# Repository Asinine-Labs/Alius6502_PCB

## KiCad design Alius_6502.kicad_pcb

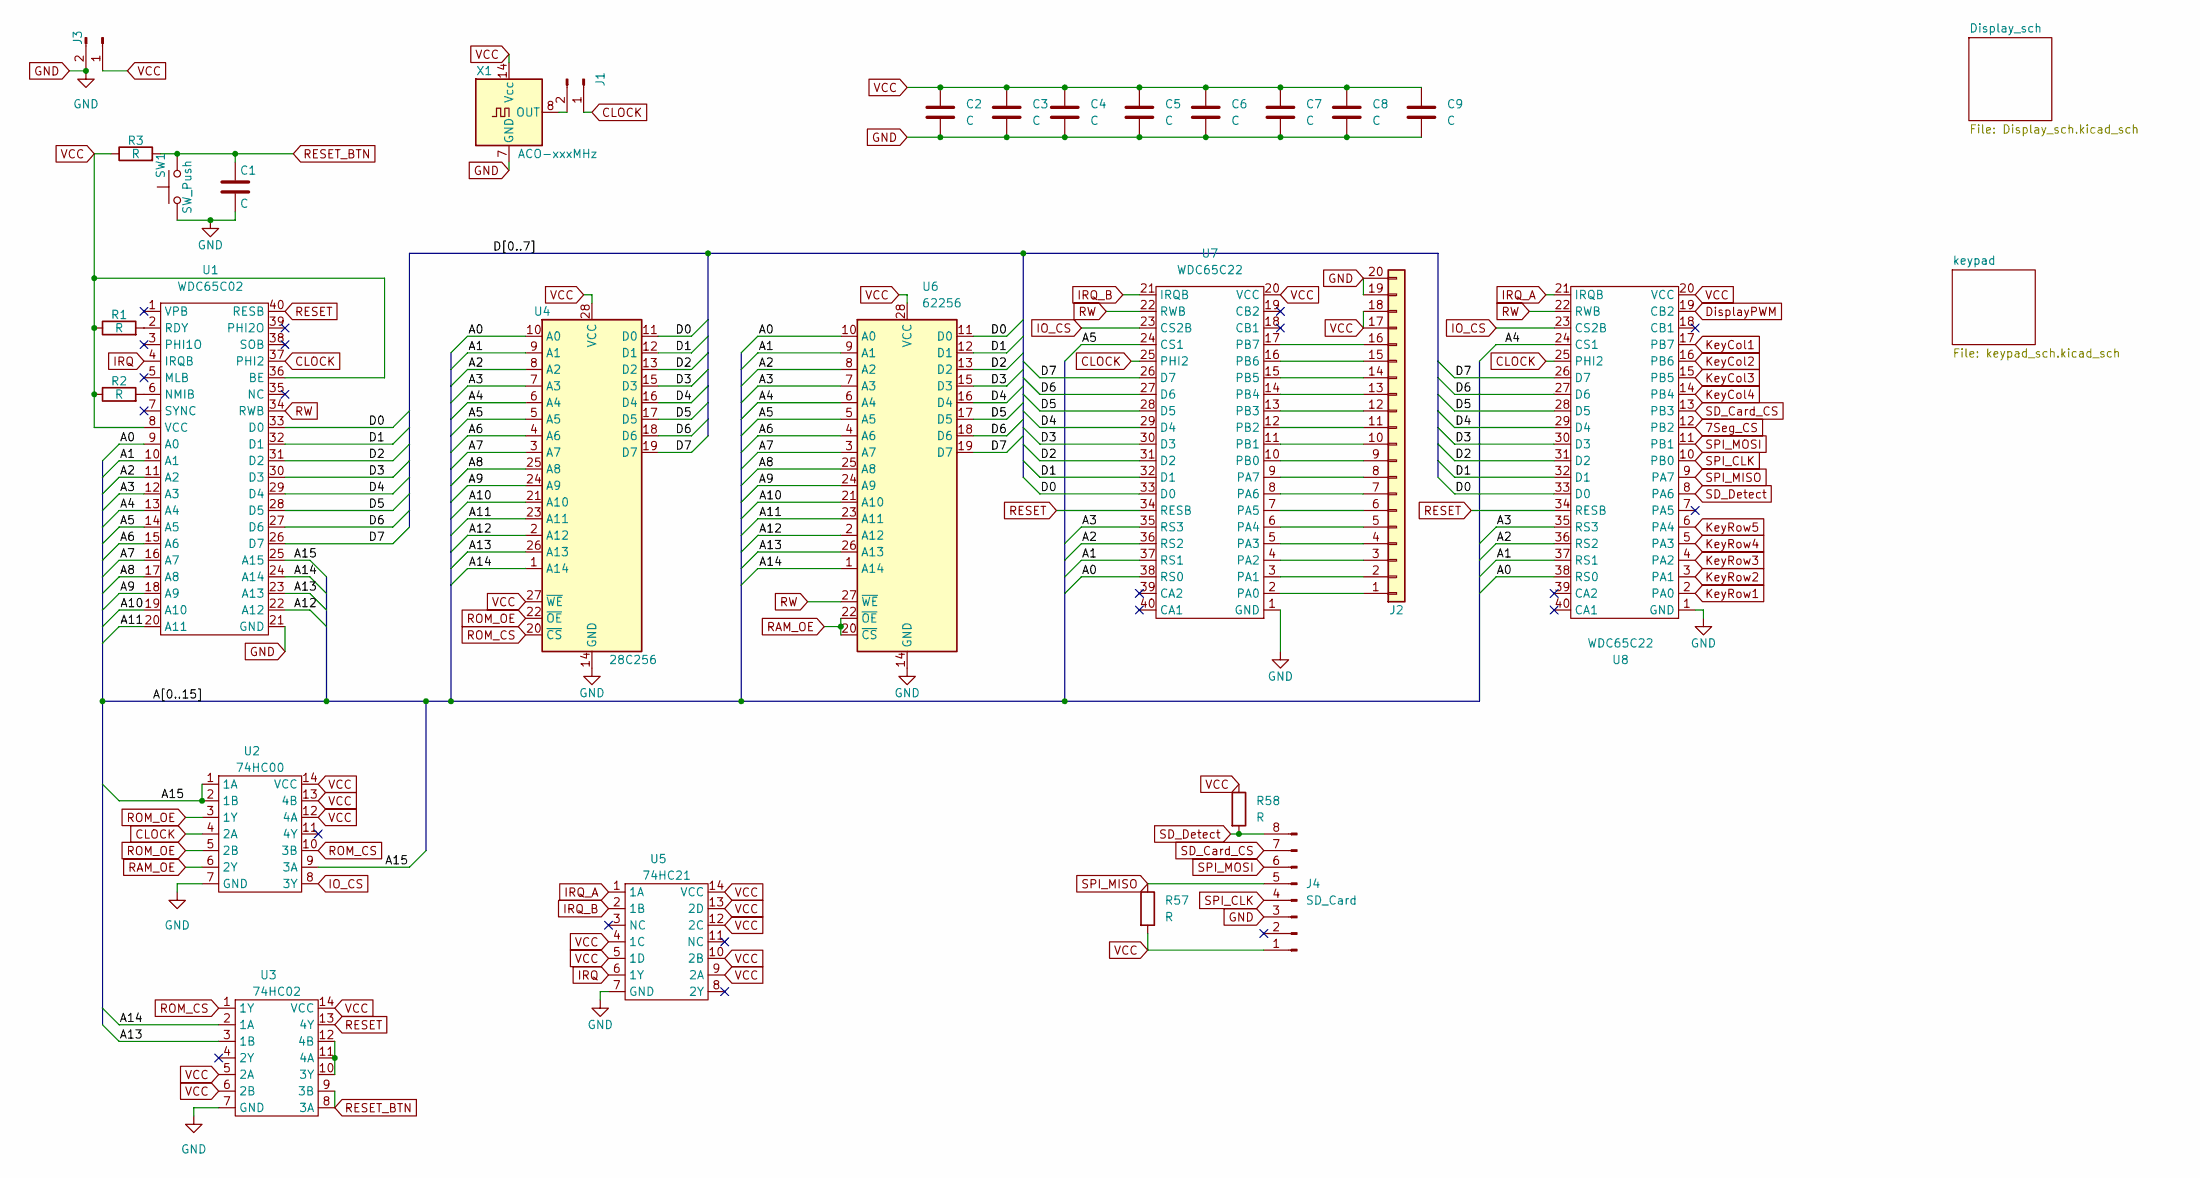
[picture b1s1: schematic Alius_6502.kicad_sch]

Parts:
C1: C; CP_Radial_D6.3mm_P2.50mm
C2, C3, C4, C5, C6, C7, C8, C9: C; C_Axial_L3.8mm_D2.6mm_P7.50mm_Horizontal
J1: Conn_01x02_Male; 2_pin_header
J2: Conn_01x20; 20pin header
J3: Power; 2_pin_header
J4: SD_Card; SD_Card_Header
R1, R2, R3, R57, R58: R; R_Axial_DIN0207_L6.3mm_D2.5mm_P10.16mm_Horizontal
SW1: SW_Push; push_switch
U1: WDC65C02; 40-pin-DIP
U2: 74HC00; DIP-14_W7.62mm_Socket_LongPads
U3: 74HC02; DIP-14_W7.62mm_Socket_LongPads
U4: 28C256; 28-pin-DIP
U5: 74HC21; DIP-14_W7.62mm_Socket_LongPads
U6: 62256; 28-pin-DIP
U7, U8: WDC65C22; 40-pin-DIP
X1: ACO-xxxMHz; Oscillator_DIP-14

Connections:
7Seg_CS: U8.12 (PB2); also elsewhere on the board
/A0: U1.9 (A0), U4.10 (A0), U6.10 (A0), U7.38 (RS0), U8.38 (RS0)
/A1: U1.10 (A1), U4.9 (A1), U6.9 (A1), U7.37 (RS1), U8.37 (RS1)
/A2: U1.11 (A2), U4.8 (A2), U6.8 (A2), U7.36 (RS2), U8.36 (RS2)
/A3: U1.12 (A3), U4.7 (A3), U6.7 (A3), U7.35 (RS3), U8.35 (RS3)
/A4: U1.13 (A4), U4.6 (A4), U6.6 (A4), U8.24 (CS1)
/A5: U1.14 (A5), U4.5 (A5), U6.5 (A5), U7.24 (CS1)
/A6: U1.15 (A6), U4.4 (A6), U6.4 (A6)
/A7: U1.16 (A7), U4.3 (A7), U6.3 (A7)
/A8: U1.17 (A8), U4.25 (A8), U6.25 (A8)
/A9: U1.18 (A9), U4.24 (A9), U6.24 (A9)
/A10: U1.19 (A10), U4.21 (A10), U6.21 (A10)
/A11: U1.20 (A11), U4.23 (A11), U6.23 (A11)
/A12: U1.22 (A12), U4.2 (A12), U6.2 (A12)
/A13: U1.23 (A13), U3.3 (1B), U4.26 (A13), U6.26 (A13)
/A14: U1.24 (A14), U3.2 (1A), U4.1 (A14), U6.1 (A14)
/A15: U1.25 (A15), U2.1 (1A), U2.2 (1B), U2.9 (3A)
/D0: U1.33 (D0), U4.11 (D0), U6.11 (D0), U7.33 (D0), U8.33 (D0)
/D1: U1.32 (D1), U4.12 (D1), U6.12 (D1), U7.32 (D1), U8.32 (D1)
/D2: U1.31 (D2), U4.13 (D2), U6.13 (D2), U7.31 (D2), U8.31 (D2)
/D3: U1.30 (D3), U4.15 (D3), U6.15 (D3), U7.30 (D3), U8.30 (D3)
/D4: U1.29 (D4), U4.16 (D4), U6.16 (D4), U7.29 (D4), U8.29 (D4)
/D5: U1.28 (D5), U4.17 (D5), U6.17 (D5), U7.28 (D5), U8.28 (D5)
/D6: U1.27 (D6), U4.18 (D6), U6.18 (D6), U7.27 (D6), U8.27 (D6)
/D7: U1.26 (D7), U4.19 (D7), U6.19 (D7), U7.26 (D7), U8.26 (D7)
CLOCK: J1.1, U1.37 (PHI2), U2.4 (2A), U7.25 (PHI2), U8.25 (PHI2)
DisplayPWM: U8.19 (CB2); also elsewhere on the board
GND: C1.2, C2.2, C3.2, C4.2, C5.2, C6.2, C7.2, C8.2, C9.2, J2.19, J2.20, J3.2, J4.3, SW1.1, U1.21 (GND), U2.7 (GND), U3.7 (GND), U4.14 (GND), U5.7 (GND), U6.14 (GND), U7.1 (GND), U8.1 (GND), X1.7 (GND); also elsewhere on the board
IO_CS: U2.8 (3Y), U7.23 (CS2B), U8.23 (CS2B)
IRQ: U1.4 (IRQB), U5.6 (1Y)
IRQ_A: U5.1 (1A), U8.21 (IRQB)
IRQ_B: U5.2 (1B), U7.21 (IRQB)
KeyCol1: U8.17 (PB7); also elsewhere on the board
KeyCol2: U8.16 (PB6); also elsewhere on the board
KeyCol3: U8.15 (PB5); also elsewhere on the board
KeyCol4: U8.14 (PB4); also elsewhere on the board
KeyRow1: U8.2 (PA0); also elsewhere on the board
KeyRow2: U8.3 (PA1); also elsewhere on the board
KeyRow3: U8.4 (PA2); also elsewhere on the board
KeyRow4: U8.5 (PA3); also elsewhere on the board
KeyRow5: U8.6 (PA4); also elsewhere on the board
unnamed: J1.2, X1.8 (OUT)
unnamed: J2.1, U7.2 (PA0)
unnamed: J2.2, U7.3 (PA1)
unnamed: J2.3, U7.4 (PA2)
unnamed: J2.4, U7.5 (PA3)
unnamed: J2.5, U7.6 (PA4)
unnamed: J2.6, U7.7 (PA5)
unnamed: J2.7, U7.8 (PA6)
unnamed: J2.8, U7.9 (PA7)
unnamed: J2.9, U7.10 (PB0)
unnamed: J2.10, U7.11 (PB1)
unnamed: J2.11, U7.12 (PB2)
unnamed: J2.12, U7.13 (PB3)
unnamed: J2.13, U7.14 (PB4)
unnamed: J2.14, U7.15 (PB5)
unnamed: J2.15, U7.16 (PB6)
unnamed: J2.16, U7.17 (PB7)
unnamed: R2.2, U1.6 (NMIB)
unnamed: R1.2, U1.2 (RDY)
unnamed: U3.10 (3Y), U3.11 (4A), U3.12 (4B)
RAM_OE: U2.6 (2Y), U6.20 (~CS), U6.22 (~OE)
RESET: U1.40 (RESB), U3.13 (4Y), U7.34 (RESB), U8.34 (RESB); also elsewhere on the board
RESET_BTN: C1.1, R3.2, SW1.2, U3.8 (3A), U3.9 (3B)
ROM_CS: U2.10 (3B), U3.1 (1Y), U4.20 (~CS)
ROM_OE: U2.3 (1Y), U2.5 (2B), U4.22 (~OE)
RW: U1.34 (RWB), U6.27 (~WE), U7.22 (RWB), U8.22 (RWB)
SD_Card_CS: J4.7, U8.13 (PB3)
SD_Detect: J4.8, R58.2, U8.8 (PA6)
SPI_CLK: J4.4, U8.10 (PB0); also elsewhere on the board
SPI_MISO: J4.5, R57.1, U8.9 (PA7)
SPI_MOSI: J4.6, U8.11 (PB1); also elsewhere on the board
VCC: C2.1, C3.1, C4.1, C5.1, C6.1, C7.1, C8.1, C9.1, J2.17, J2.18, J3.1, J4.1, R1.1, R2.1, R3.1, R57.2, R58.1, U1.8 (VCC), U1.36 (BE), U2.12 (4A), U2.13 (4B), U2.14 (VCC), U3.5 (2A), U3.6 (2B), U3.14 (VCC), U4.27 (~WE), U4.28 (VCC), U5.4 (1C), U5.5 (1D), U5.9 (2A), U5.10 (2B), U5.12 (2C), U5.13 (2D), U5.14 (VCC), U6.28 (VCC), U7.20 (VCC), U8.20 (VCC), X1.14 (Vcc); also elsewhere on the board

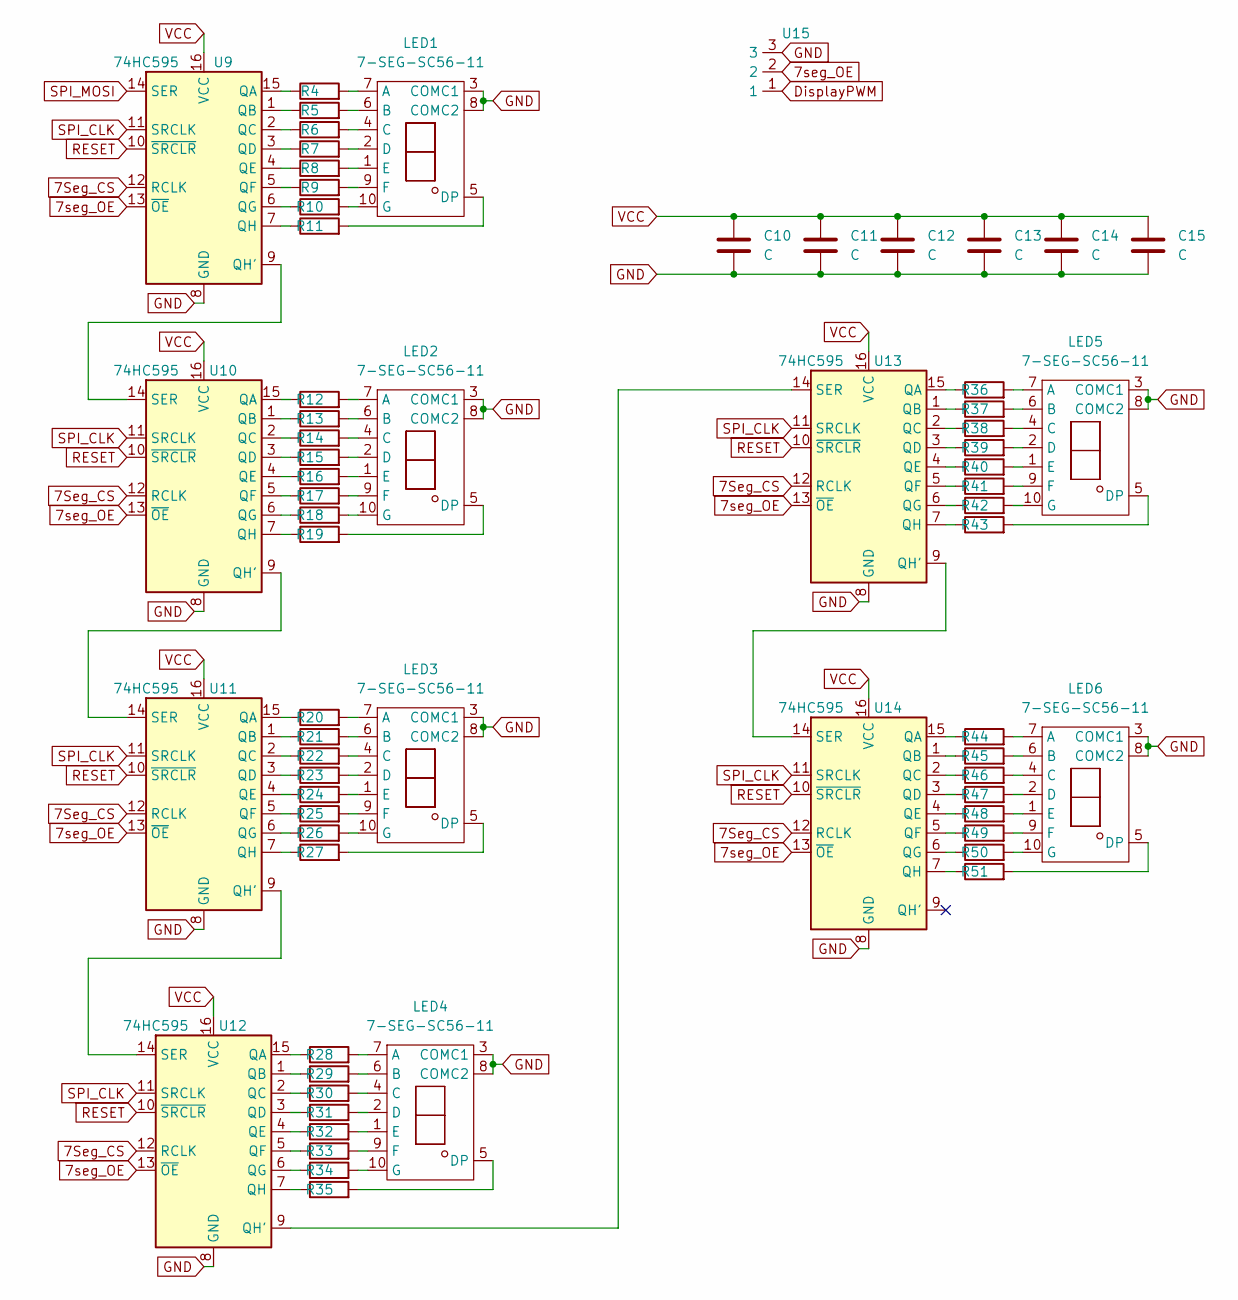
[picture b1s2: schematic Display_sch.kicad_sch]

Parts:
C10, C11, C12, C13, C14, C15: C; C_Axial_L3.8mm_D2.6mm_P7.50mm_Horizontal
LED1, LED2, LED3, LED4, LED5, LED6: 7-SEG-SC56-11; 7-seg
R4, R5, R6, R7, R8, R9, R10, R11, R12, R13, R14, R15, R16, R17, R18, R19, R20, R21, R22, R23, R24, R25, R26, R27, R28, R29, R30, R31, R32, R33, R34, R35, R36, R37, R38, R39, R40, R41, R42, R43, R44, R45, R46, R47, R48, R49, R50, R51: R; R_Axial_DIN0207_L6.3mm_D2.5mm_P10.16mm_Horizontal
U9, U10, U11, U12, U13, U14: 74HC595; DIP-16_W7.62mm_LongPads
U15: 3_pin_header

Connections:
7Seg_CS: U9.12 (RCLK), U10.12 (RCLK), U11.12 (RCLK), U12.12 (RCLK), U13.12 (RCLK), U14.12 (RCLK); also elsewhere on the board
7seg_OE: U9.13 (~OE), U10.13 (~OE), U11.13 (~OE), U12.13 (~OE), U13.13 (~OE), U14.13 (~OE), U15.2; also elsewhere on the board
GND: C10.2, C11.2, C12.2, C13.2, C14.2, C15.2, LED1.3 (COMC1), LED1.8 (COMC2), LED2.3 (COMC1), LED2.8 (COMC2), LED3.3 (COMC1), LED3.8 (COMC2), LED4.3 (COMC1), LED4.8 (COMC2), LED5.3 (COMC1), LED5.8 (COMC2), LED6.3 (COMC1), LED6.8 (COMC2), U9.8 (GND), U10.8 (GND), U11.8 (GND), U12.8 (GND), U13.8 (GND), U14.8 (GND), U15.3; also elsewhere on the board
unnamed: LED1.7 (A), R4.2
unnamed: LED1.6 (B), R5.2
unnamed: LED1.4 (C), R6.2
unnamed: LED1.2 (D), R7.2
unnamed: LED1.5 (DP), R11.2
unnamed: LED1.1 (E), R8.2
unnamed: LED1.9 (F), R9.2
unnamed: LED1.10 (G), R10.2
unnamed: LED2.7 (A), R12.2
unnamed: LED2.6 (B), R13.2
unnamed: LED2.4 (C), R14.2
unnamed: LED2.2 (D), R15.2
unnamed: LED2.5 (DP), R19.2
unnamed: LED2.1 (E), R16.2
unnamed: LED2.9 (F), R17.2
unnamed: LED2.10 (G), R18.2
unnamed: LED3.7 (A), R20.2
unnamed: LED3.6 (B), R21.2
unnamed: LED3.4 (C), R22.2
unnamed: LED3.2 (D), R23.2
unnamed: LED3.5 (DP), R27.2
unnamed: LED3.1 (E), R24.2
unnamed: LED3.9 (F), R25.2
unnamed: LED3.10 (G), R26.2
unnamed: LED4.7 (A), R28.2
unnamed: LED4.6 (B), R29.2
unnamed: LED4.4 (C), R30.2
unnamed: LED4.2 (D), R31.2
unnamed: LED4.5 (DP), R35.2
unnamed: LED4.1 (E), R32.2
unnamed: LED4.9 (F), R33.2
unnamed: LED4.10 (G), R34.2
unnamed: LED5.7 (A), R36.2
unnamed: LED5.6 (B), R37.2
unnamed: LED5.4 (C), R38.2
unnamed: LED5.2 (D), R39.2
unnamed: LED5.5 (DP), R43.2
unnamed: LED5.1 (E), R40.2
unnamed: LED5.9 (F), R41.2
unnamed: LED5.10 (G), R42.2
unnamed: LED6.7 (A), R44.2
unnamed: LED6.6 (B), R45.2
unnamed: LED6.4 (C), R46.2
unnamed: LED6.2 (D), R47.2
unnamed: LED6.5 (DP), R51.2
unnamed: LED6.1 (E), R48.2
unnamed: LED6.9 (F), R49.2
unnamed: LED6.10 (G), R50.2
unnamed: R4.1, U9.15 (QA)
unnamed: R5.1, U9.1 (QB)
unnamed: R6.1, U9.2 (QC)
unnamed: R7.1, U9.3 (QD)
unnamed: R8.1, U9.4 (QE)
unnamed: R9.1, U9.5 (QF)
unnamed: R10.1, U9.6 (QG)
unnamed: R11.1, U9.7 (QH)
unnamed: R12.1, U10.15 (QA)
unnamed: R13.1, U10.1 (QB)
unnamed: R14.1, U10.2 (QC)
unnamed: R15.1, U10.3 (QD)
unnamed: R16.1, U10.4 (QE)
unnamed: R17.1, U10.5 (QF)
unnamed: R18.1, U10.6 (QG)
unnamed: U10.9 (QH'), U11.14 (SER)
unnamed: R19.1, U10.7 (QH)
unnamed: U9.9 (QH'), U10.14 (SER)
unnamed: R20.1, U11.15 (QA)
unnamed: R21.1, U11.1 (QB)
unnamed: R22.1, U11.2 (QC)
unnamed: R23.1, U11.3 (QD)
unnamed: R24.1, U11.4 (QE)
unnamed: R25.1, U11.5 (QF)
unnamed: R26.1, U11.6 (QG)
unnamed: U11.9 (QH'), U12.14 (SER)
unnamed: R27.1, U11.7 (QH)
unnamed: R28.1, U12.15 (QA)
unnamed: R29.1, U12.1 (QB)
unnamed: R30.1, U12.2 (QC)
unnamed: R31.1, U12.3 (QD)
unnamed: R32.1, U12.4 (QE)
unnamed: R33.1, U12.5 (QF)
unnamed: R34.1, U12.6 (QG)
unnamed: U12.9 (QH'), U13.14 (SER)
unnamed: R35.1, U12.7 (QH)
unnamed: R36.1, U13.15 (QA)
unnamed: R37.1, U13.1 (QB)
unnamed: R38.1, U13.2 (QC)
unnamed: R39.1, U13.3 (QD)
unnamed: R40.1, U13.4 (QE)
unnamed: R41.1, U13.5 (QF)
unnamed: R42.1, U13.6 (QG)
unnamed: U13.9 (QH'), U14.14 (SER)
unnamed: R43.1, U13.7 (QH)
unnamed: R44.1, U14.15 (QA)
unnamed: R45.1, U14.1 (QB)
unnamed: R46.1, U14.2 (QC)
unnamed: R47.1, U14.3 (QD)
unnamed: R48.1, U14.4 (QE)
unnamed: R49.1, U14.5 (QF)
unnamed: R50.1, U14.6 (QG)
unnamed: R51.1, U14.7 (QH)
RESET: U9.10 (~SRCLR), U10.10 (~SRCLR), U11.10 (~SRCLR), U12.10 (~SRCLR), U13.10 (~SRCLR), U14.10 (~SRCLR); also elsewhere on the board
SPI_CLK: U9.11 (SRCLK), U10.11 (SRCLK), U11.11 (SRCLK), U12.11 (SRCLK), U13.11 (SRCLK), U14.11 (SRCLK); also elsewhere on the board
SPI_MOSI: U9.14 (SER); also elsewhere on the board
VCC: C10.1, C11.1, C12.1, C13.1, C14.1, C15.1, U9.16 (VCC), U10.16 (VCC), U11.16 (VCC), U12.16 (VCC), U13.16 (VCC), U14.16 (VCC); also elsewhere on the board

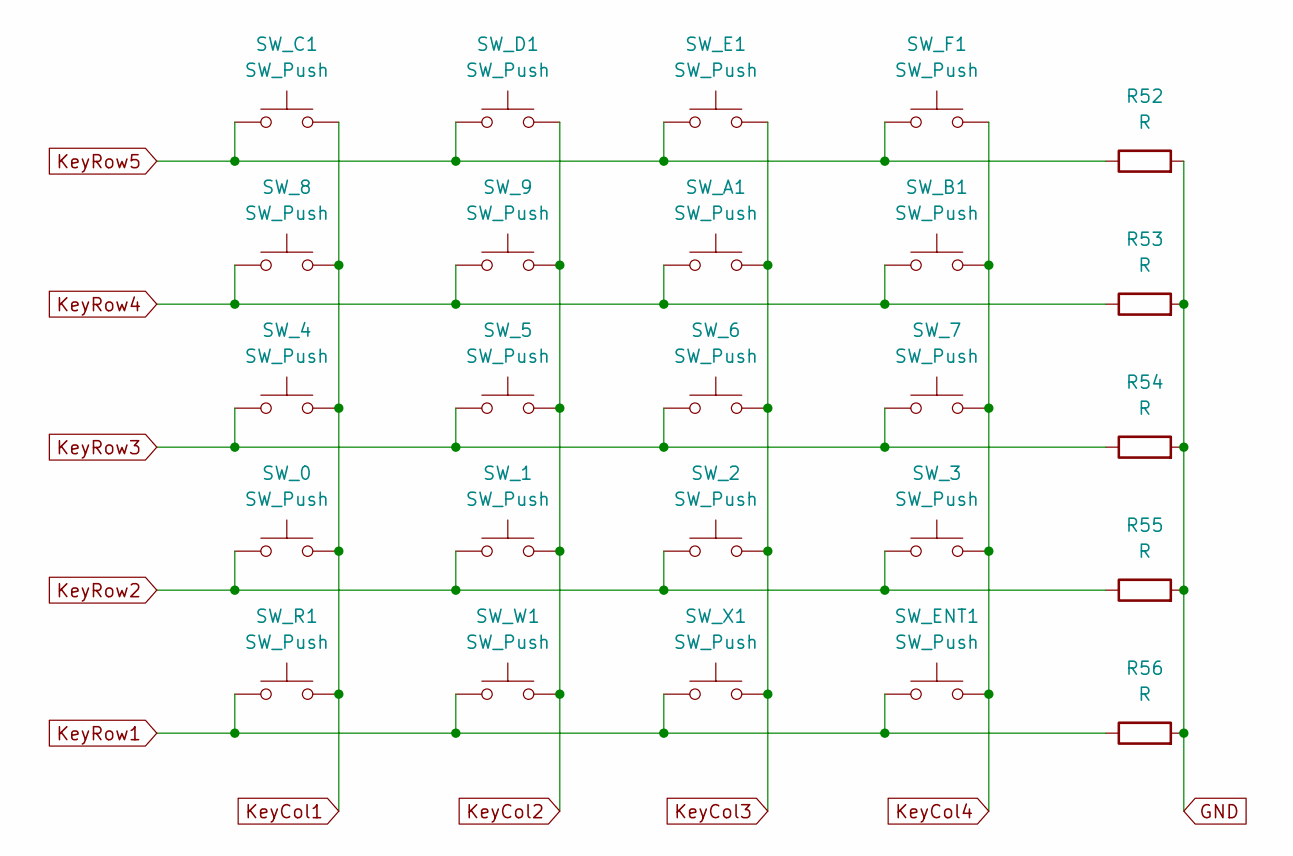
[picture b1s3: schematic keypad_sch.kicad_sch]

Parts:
R52, R53, R54, R55, R56: R; R_Axial_DIN0207_L6.3mm_D2.5mm_P10.16mm_Horizontal
SW_0, SW_1, SW_2, SW_3, SW_4, SW_5, SW_6, SW_7, SW_8, SW_9: SW_Push; Kailh CHOC Low Profile
SW_A1: SW_Push; Kailh CHOC Low Profile
SW_B1: SW_Push; Kailh CHOC Low Profile
SW_C1: SW_Push; Kailh CHOC Low Profile
SW_D1: SW_Push; Kailh CHOC Low Profile
SW_E1: SW_Push; Kailh CHOC Low Profile
SW_ENT1: SW_Push; Kailh CHOC Low Profile
SW_F1: SW_Push; Kailh CHOC Low Profile
SW_R1: SW_Push; Kailh CHOC Low Profile
SW_W1: SW_Push; Kailh CHOC Low Profile
SW_X1: SW_Push; Kailh CHOC Low Profile

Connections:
GND: R52.2, R53.2, R54.2, R55.2, R56.2; also elsewhere on the board
KeyCol1: SW_0.2, SW_4.2, SW_8.2, SW_C1.2, SW_R1.2; also elsewhere on the board
KeyCol2: SW_1.2, SW_5.2, SW_9.2, SW_D1.2, SW_W1.2; also elsewhere on the board
KeyCol3: SW_2.2, SW_6.2, SW_A1.2, SW_E1.2, SW_X1.2; also elsewhere on the board
KeyCol4: SW_3.2, SW_7.2, SW_B1.2, SW_ENT1.2, SW_F1.2; also elsewhere on the board
KeyRow1: R56.1, SW_ENT1.1, SW_R1.1, SW_W1.1, SW_X1.1; also elsewhere on the board
KeyRow2: R55.1, SW_0.1, SW_1.1, SW_2.1, SW_3.1; also elsewhere on the board
KeyRow3: R54.1, SW_4.1, SW_5.1, SW_6.1, SW_7.1; also elsewhere on the board
KeyRow4: R53.1, SW_8.1, SW_9.1, SW_A1.1, SW_B1.1; also elsewhere on the board
KeyRow5: R52.1, SW_C1.1, SW_D1.1, SW_E1.1, SW_F1.1; also elsewhere on the board

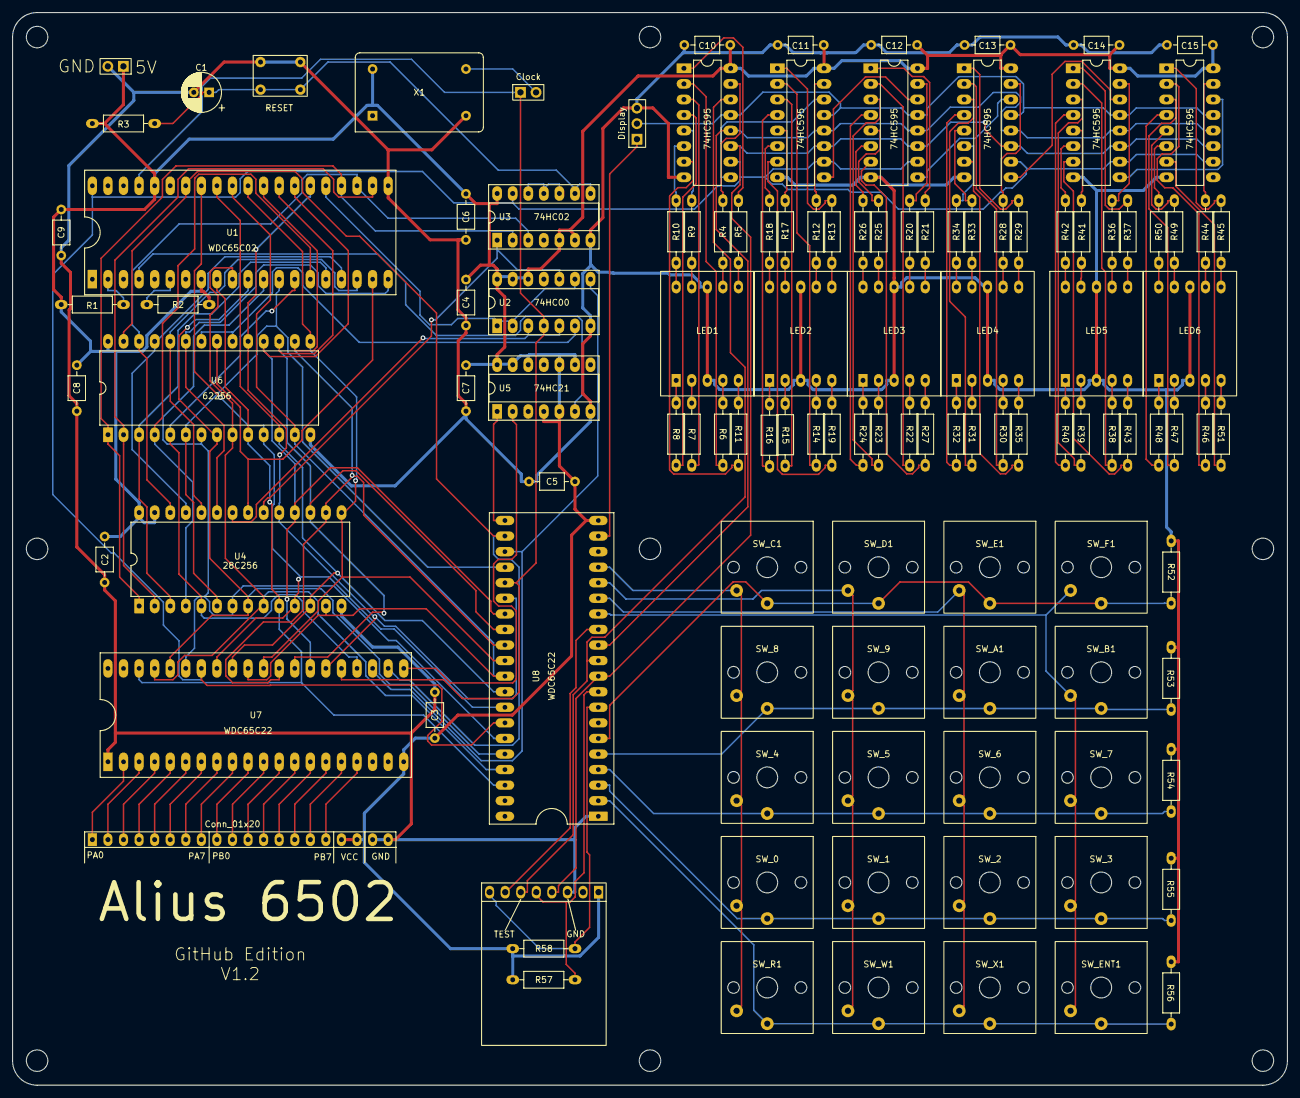
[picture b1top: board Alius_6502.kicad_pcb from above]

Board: 2 copper layers, 208.0 x 175.0 mm, 129 parts (0 on the bottom side), 175 nets.

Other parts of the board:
Display: 3_pin_header
HOLE1, HOLE2, HOLE4, HOLE5, HOLE6, HOLE7, HOLE8, HOLE9: MountingHole_3.5mm
Hole3: MountingHole_3.5mm

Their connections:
7seg_OE: Display.2; also elsewhere on the board
DisplayPWM: Display.1; also elsewhere on the board
GND: Display.3; also elsewhere on the board

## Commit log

2023-06-19 Tidy up of track routing to give more clearance. Tidy up missing silkscreen of chip numbers.
2023-07-13 Added PNG images of Schematic and final PCB
2024-02-09 Version 1.2
    Improved reset.
    Added connection for PWM display brightness.
    NOTE: This board revision is yet to be made and tested.
2024-02-24 Version 1.2
    Improved reset circuit.
    Support for software brightness.
